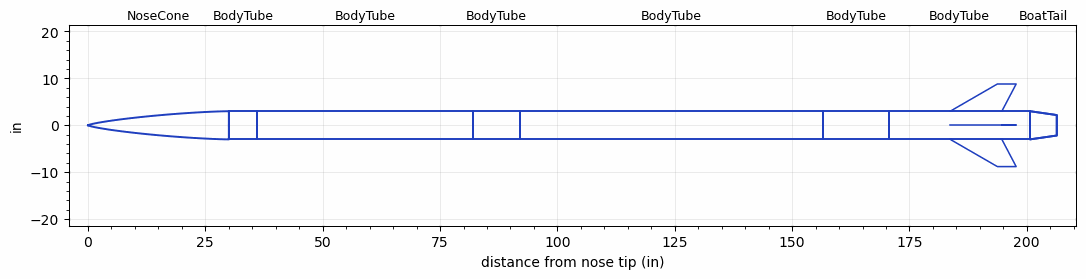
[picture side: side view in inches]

<RASAeroDocument>
 <FileVersion>2</FileVersion>
 <RocketDesign>
  <NoseCone>
   <Length>30</Length>
   <Diameter>6</Diameter>
   <Shape>Von Karman Ogive</Shape>
   <Location>0</Location>
  </NoseCone>
  <BodyTube>
   <Length>6</Length>
   <Diameter>6</Diameter>
   <Location>30</Location>
  </BodyTube>
  <BodyTube>
   <Length>46</Length>
   <Diameter>6</Diameter>
   <Location>36</Location>
  </BodyTube>
  <BodyTube>
   <Length>10</Length>
   <Diameter>6</Diameter>
   <Location>82</Location>
  </BodyTube>
  <BodyTube>
   <Length>64.69</Length>
   <Diameter>6</Diameter>
   <Location>92</Location>
  </BodyTube>
  <BodyTube>
   <Length>14</Length>
   <Diameter>6</Diameter>
   <Location>156.69</Location>
  </BodyTube>
  <BodyTube>
   <Length>30</Length>
   <Diameter>6</Diameter>
   <Location>170.69</Location>
   <BoattailLength>5.7</BoattailLength>
   <BoattailRearDiameter>4.36</BoattailRearDiameter>
   <Fin>
    <Count>4</Count>
    <Chord>11</Chord>
    <Span>5.8</Span>
    <SweepDistance>10.046</SweepDistance>
    <TipChord>4</TipChord>
    <Thickness>0.3</Thickness>
    <LERadius>0.01</LERadius>
    <Location>17</Location>
    <AirfoilSection>Hexagonal</AirfoilSection>
    <FX1>0.3</FX1>
    <FX3>0.3</FX3>
   </Fin>
  </BodyTube>
  <BoatTail>
   <Length>5.7</Length>
   <Diameter>6</Diameter>
   <RearDiameter>4.36</RearDiameter>
   <Location>200.69</Location>
  </BoatTail>
  <Surface>Camouflage Paint</Surface>
  <ModifiedBarrowman>True</ModifiedBarrowman>
  <Turbulence>True</Turbulence>
  <UseBooster1>False</UseBooster1>
  <UseBooster2>False</UseBooster2>
 </RocketDesign>
 <LaunchSite>
  <Altitude>2950</Altitude>
  <Pressure>27</Pressure>
  <RodAngle>6</RodAngle>
  <RodLength>32.8</RodLength>
  <Temperature>86</Temperature>
  <WindSpeed>16</WindSpeed>
 </LaunchSite>
 <Recovery>
  <Altitude1>1000</Altitude1>
  <Altitude2>1000</Altitude2>
  <DeviceType1>None</DeviceType1>
  <DeviceType2>None</DeviceType2>
  <Event1>False</Event1>
  <Event2>False</Event2>
  <Size1>1</Size1>
  <Size2>1</Size2>
  <EventType1>None</EventType1>
  <EventType2>None</EventType2>
  <CD1>1.33</CD1>
  <CD2>1.33</CD2>
 </Recovery>
 <SimulationList>
  <Simulation>
   <SustainerEngine>COMBINED  (TAMUSRT)</SustainerEngine>
   <SustainerLaunchWt>137</SustainerLaunchWt>
   <SustainerCG>128</SustainerCG>
   <SustainerIgnitionDelay>0</SustainerIgnitionDelay>
   <Booster1SeparationDelay>0</Booster1SeparationDelay>
   <Booster1IgnitionDelay>0</Booster1IgnitionDelay>
   <IncludeBooster1>False</IncludeBooster1>
   <Booster2Delay>0</Booster2Delay>
   <IncludeBooster2>False</IncludeBooster2>
   <TimetoApogee>41.18909</TimetoApogee>
   <MaxAltitude>26784.44</MaxAltitude>
   <MaxVelocity>1625.545</MaxVelocity>
  </Simulation>
  <Simulation>
   <SustainerEngine>COMB_PLUS  (TAMUSRT)</SustainerEngine>
   <SustainerLaunchWt>128</SustainerLaunchWt>
   <SustainerCG>125</SustainerCG>
   <SustainerIgnitionDelay>0</SustainerIgnitionDelay>
   <Booster1SeparationDelay>0</Booster1SeparationDelay>
   <Booster1IgnitionDelay>0</Booster1IgnitionDelay>
   <IncludeBooster1>False</IncludeBooster1>
   <Booster2Delay>0</Booster2Delay>
   <IncludeBooster2>False</IncludeBooster2>
   <TimetoApogee>41.71901</TimetoApogee>
   <MaxAltitude>26628.62</MaxAltitude>
   <MaxVelocity>1520.361</MaxVelocity>
  </Simulation>
  <Simulation>
   <SustainerEngine>COMBINED_30  (TAMUSRT)</SustainerEngine>
   <SustainerLaunchWt>149</SustainerLaunchWt>
   <SustainerCG>130</SustainerCG>
   <SustainerIgnitionDelay>0</SustainerIgnitionDelay>
   <Booster1SeparationDelay>0</Booster1SeparationDelay>
   <Booster1IgnitionDelay>0</Booster1IgnitionDelay>
   <IncludeBooster1>False</IncludeBooster1>
   <Booster2Delay>0</Booster2Delay>
   <IncludeBooster2>False</IncludeBooster2>
   <TimetoApogee>45.47837</TimetoApogee>
   <MaxAltitude>31800.8</MaxAltitude>
   <MaxVelocity>1696.014</MaxVelocity>
  </Simulation>
 </SimulationList>
</RASAeroDocument>
